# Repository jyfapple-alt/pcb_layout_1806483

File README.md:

# auto_routing README

这份 README 主要做两件事：

1. 用通俗的话解释这个仓库里暴露出来的 MCP tools 是干什么的。
2. 把每个 tool 的入参、返回值、参数意义讲清楚。
3. 顺带把 `.claude/skills` 里的技能做一遍“人话解读”。

这份说明是根据下面这些源码整理出来的，不是凭空猜的：

- `mcp/pcb_routing_server.py`
- `mcp/route_analysis.py`
- `mcp/route_planner.py`
- `mcp/footprint_placement.py`
- `mcp/coordinate_routing.py`
- `mcp/routing_session_store.py`
- `.claude/skills/*/SKILL.md`

---

## 1. 这个仓库的 MCP 到底是什么

这个项目里真正对外暴露 MCP tools 的入口是：

- `mcp/pcb_routing_server.py`

它用的是 `FastMCP`，名字叫：

- `pcb-routing-mcp`

你可以把它理解成一个“会操作 KiCad PCB 的本地工具服务器”。  
LLM 不直接手搓 PCB 文件，而是通过这些 tool 去做：

- 看板子结构
- 分析哪些器件要先 fanout
- 自动放置 footprint
- 生成 routing plan
- 执行自动布线
- 让 LLM 输出坐标形式的走线计划
- 校验 DRC / 连通性 / 悬空 stub

仓库里还有很多 Python 文件，但不是每个 Python 函数都算 MCP tool。  
真正的 MCP tool，是那些被 `@mcp.tool(...)` 装饰过的函数。

当前一共暴露了 **33 个 MCP tool**。

---

## 2. 整体结构怎么理解

可以把这些 tool 分成 5 组：

- **基础检查类**
  看板子、看环境、看文件是否合法。
- **Session 工作流类**
  把一次布线任务做成一个“会话”，方便多次调用之间保留上下文。
- **Footprint 放置类**
  给元件做自动摆放，或者让 LLM 自己出摆放方案。
- **坐标级布线类**
  给 LLM 一份几何上下文，让它直接输出走线点坐标。
- **底层脚本封装类**
  直接封装 `mcp/kicad_routing_tools` 里的 CLI 脚本，例如 fanout、route、DRC 检查等。

---

## 3. 通用规则

在看每个 tool 之前，先记住几个通用规则，后面会反复出现。

### 3.1 路径怎么处理

- 凡是 `pcb_path`、`input_pcb`、`board_path` 这类输入文件参数，都会先检查文件是否存在。
- 相对路径会按**仓库根目录**来解析，不是按当前 shell 所在目录。
- 输出路径参数比如 `output_path`、`output_pcb`、`output_board`，如果传相对路径，也会按仓库根目录解析。

### 3.2 日志放哪里

底层脚本类 tool 会把输出写进：

- `mcp/logs/`

返回里通常会带一个：

- `log_path`

如果自动布线失败，优先看这个日志路径最省事。

### 3.3 Session 放哪里

路由会话会保存在：

- `mcp/routing_sessions/<session_id>/`

每个 session 里会保存：

- 当前工作板文件
- 分析结果
- 路由计划
- 执行历史
- 最近几次校验结果
- 放置/坐标上下文
- 产物路径和日志路径

### 3.4 底层脚本封装的通用返回结构

下面这些 tool 都走统一的 `_run_script(...)` 返回格式：

- `run_routing_script`
- `build_rust_router`
- `list_nets`
- `run_bga_fanout`
- `run_qfn_fanout`
- `route_single_ended`
- `route_differential_pairs`
- `create_power_planes`
- `repair_disconnected_planes`
- `check_connectivity`
- `check_drc`
- `check_orphan_stubs`

它们的返回字段基本一致：

- `success`
  是否成功，底层进程退出码为 0 时通常为 `true`。
- `script`
  实际调用的脚本名，例如 `route.py`。
- `command`
  实际执行的命令数组。
- `cwd`
  运行脚本时的工作目录。
- `returncode`
  底层进程退出码。超时场景会是 `null`。
- `duration_seconds`
  运行耗时。
- `stdout_tail`
  标准输出的最后一段内容。
- `stderr_tail`
  标准错误的最后一段内容。
- `log_path`
  完整日志文件路径。
- `json_summary`
  如果脚本输出了 `JSON_SUMMARY:` 行，这里会解析成 JSON；否则为 `null`。
- `timed_out`
  只有超时返回时才会出现，值为 `true`。

一句话理解：  
这类 tool 负责“跑脚本”，所以重点看 `success`、`log_path`、`json_summary`。

---

## 4. 几个高频数据结构先看懂

后面的 tool 会反复返回这些结构。

### 4.1 Session 对象

`create_routing_session` 和 `get_routing_session` 返回的是完整 session 对象，核心字段有：

- `session_id`
  会话 ID，例如 `rs_xxxxx`。
- `session_name`
  会话显示名。
- `description`
  会话说明。
- `board_path`
  原始板文件路径。
- `working_board_path`
  当前正在操作的板文件路径。后续每做一步，通常都是它在变化。
- `coordinate_mode`
  坐标模式。当前最有意义的是：
  - `algorithm_only`：主要靠算法路由器
  - `llm_coordinates`：允许 LLM 直接给坐标走线
- `placement_mode`
  放置模式。当前最常见的是：
  - `auto`
  - `llm_placement`
- `status`
  当前状态，例如 `created`、`analyzed`、`planned`、`placed`、`executed` 等。
- `created_at` / `updated_at`
  创建和更新时间。
- `session_dir`
  这个 session 自己的目录。
- `output_dir`
  这个 session 默认的输出目录。
- `analysis`
  上一次结构化分析结果。
- `objective`
  这次规划的目标，比如 `autoroute`。
- `constraints`
  规划时使用的约束。
- `proposed_plan`
  上一次生成的 routing plan。
- `execution_history`
  历史执行记录。
- `latest_checks`
  最近一次连通性 / DRC / orphan stub 检查结果。
- `placement_context`
  LLM 放置上下文。
- `latest_placement_validation`
  最近一次摆放方案校验结果。
- `placement_history`
  摆放历史。
- `coordinate_context`
  LLM 坐标布线上下文。
- `latest_coordinate_validation`
  最近一次坐标计划校验结果。
- `coordinate_history`
  坐标布线历史。
- `artifacts`
  产物路径集合，至少包含 `boards` 和 `logs`。
- `notes`
  会话过程中的注释日志。

### 4.2 `analysis` 结构

`analyze_board_for_llm` 返回的核心是 `analysis`，里面常见字段有：

- `pcb_path`
- `board`
  - `total_nets`
  - `named_nets`
  - `total_footprints`
  - `total_segments`
  - `total_vias`
  - `total_zones`
  - `fresh_board`
  - `copper_layers`
  - `board_bounds`
- `zones`
  每个 zone 的 `net_id`、`net_name`、`layer`、`layers`
- `nets`
  每个命名网络的 `net_id`、`name`、`pad_count`
- `ground_nets`
- `power_nets`
- `differential_pairs`
- `fanout_candidates`
  候选密脚器件，包含 `reference`、`footprint`、`pad_count`、`recommended_tool`
- `unrouted_named_nets`
- `high_speed_hints`
  包含 `highest_tier` 和 `matched_nets`
- `placement_hints`
  包含：
  - `footprints_at_origin`
  - `footprints_outside_board`
  - `collapsed_groups`
  - `suggested_refs`
  - `needs_placement`
- `planning_hints`
  包含：
  - `has_existing_ground_zone`
  - `has_diff_pairs`
  - `needs_fanout`
  - `needs_plane_repair_after_routing`
  - `suggested_routing_layers`
  - `suggested_power_nets_for_wide_traces`

### 4.3 `plan` 结构

`propose_routing_plan` 里的 `plan` 长这样：

- `plan_id`
- `generated_at`
- `objective`
- `coordinate_mode`
- `constraints`
- `analysis_snapshot`
  这是分析结果的浓缩版，不是全量 `analysis`
- `steps`
  每一步都是：
  - `step_id`
  - `kind`
  - `reason`
  - `input_board`
  - `output_board`
  - `parameters`

### 4.4 `placement_plan` 结构

LLM 摆放方案需要长这样：

```json
{
  "grid_step": 0.25,
  "placements": [
    {
      "reference": "U1",
      "x": 40.0,
      "y": 42.0,
      "rotation": 0.0
    }
  ]
}
```

字段含义：

- `grid_step`
  建议摆放网格。
- `placements`
  摆放列表。
- `reference`
  器件位号。
- `x` / `y`
  KiCad footprint 原点坐标，不一定是器件物理中心。
- `rotation`
  角度，单位度。

### 4.5 放置校验结果 `validation`

放置类校验结果常见字段：

- `valid`
- `pcb_path`
- `placement_gap`
- `board_margin`
- `placement_count`
- `errors`
- `warnings`
- `placements`
  每个 placement 的摘要，通常包含 `reference`、`x`、`y`、`rotation`、`width`、`height`

### 4.6 `coordinate_plan` 结构

LLM 坐标走线计划需要长这样：

```json
{
  "default_track_width": 0.1,
  "default_via_size": 0.3,
  "default_via_drill": 0.2,
  "grid_step": 0.1,
  "routes": [
    {
      "net": "/EN",
      "track_width": 0.15,
      "points": [
        {"x": 40.5, "y": 22.4, "layer": "F.Cu"},
        {"x": 42.1, "y": 22.4, "layer": "F.Cu"},
        {"x": 42.7, "y": 23.0, "layer": "F.Cu"},
        {"x": 42.7, "y": 24.6, "layer": "F.Cu"},
        {"x": 42.7, "y": 24.6, "layer": "B.Cu"},
        {"x": 44.3, "y": 24.6, "layer": "B.Cu"}
      ]
    }
  ]
}
```

字段含义：

- `default_track_width` / `default_via_size` / `default_via_drill`
  默认线宽和过孔参数。
- `grid_step`
  推荐坐标栅格。
- `routes`
  一组要新加的线路。
- `net`
  网络名。
- `track_width`
  该条 route 自己的线宽。
- `points`
  走线路径点。

注意：

- 相邻两个点 XY 相同但 layer 不同，表示“这里插一个 via”。
- 同层转角不能是直角或更尖，推荐 45 度斜切形成 135 度内角。

### 4.7 坐标校验结果 `validation`

坐标布线校验结果常见字段：

- `valid`
- `pcb_path`
- `defaults`
- `route_summaries`
- `tracks`
- `vias`
- `errors`
- `warnings`
- `normalized_plan`

### 4.8 文件合法性校验 `file_validation`

`validate_kicad_pcb` 以及坐标/摆放 apply 成功后附带的文件校验，核心字段有：

- `valid`
- `pcb_path`
- `kicad_version`
- `net_syntax_mode`
  - `numeric`
  - `name-only`
- `parse_ok`
- `parse_error`
- `pcbnew`
  - `available`
  - `ok`
  - `error`
- `issues`
  常见问题码：
  - `named-net-syntax-in-kicad9`
  - `numeric-net-syntax-in-kicad10`
  - `parser-error`
  - `pcbnew-load-error`

---

## 5. 每个 MCP tool 是干什么的

下面按类别逐个解释。

---

## 5.1 基础检查类

### `inspect_pcb`

**作用**  
快速看一块 `.kicad_pcb` 的整体情况，适合“先摸底”。

**参数**

- `pcb_path` (`str`, 必填)
  要检查的板文件路径。

**返回**

- `pcb_path`
  解析后的绝对路径。
- `total_nets`
- `total_footprints`
- `total_segments`
- `total_vias`
- `total_zones`
- `fresh_board`
  如果没有 track segment，会认为是“新板”。
- `copper_layers`
  板上铜层名列表。
- `zones`
  每个 zone 的摘要。
- `fanout_candidates`
  可能需要先做 fanout 的器件。
- `high_speed_hints`
  高速网络提示。
- `footprints`
  每个 footprint 的简要列表。

**补充说明**

- 这里的 `fanout_candidates[].recommended_tool` 返回的是脚本名：
  - `qfn_fanout.py`
  - `bga_fanout.py`
- 在 session 分析里，类似字段会返回 MCP tool 名：
  - `run_qfn_fanout`
  - `run_bga_fanout`

---

### `router_environment_status`

**作用**  
检查当前 Python 环境、嵌入式工具目录、Rust router 模块是否可用。

**参数**

- 无参数。

**返回**

- `python_executable`
  当前 Python 解释器。
- `project_root`
- `mcp_root`
- `embedded_tools_root`
- `tools_root`
  当前实际使用的工具目录。
- `tools_root_source`
  来源，通常是 `embedded` 或 `env`。
- `tools_root_exists`
- `rust_router_root`
- `rust_router_root_exists`
- `grid_router_module_exists`
- `grid_router_importable`
  能不能 import `grid_router`。
- `grid_router_version`
  仅 import 成功时返回。
- `grid_router_file`
  仅 import 成功时返回。
- `grid_router_error`
  import 失败时返回错误信息。

---

### `validate_kicad_pcb`

**作用**  
检查一个 `.kicad_pcb` 文件在当前 KiCad 版本语法下是不是合法，并尝试解析它。

**参数**

- `pcb_path` (`str`, 必填)
  要校验的板文件。
- `use_pcbnew_if_available` (`bool`, 默认 `false`)
  如果环境里有 `pcbnew`，是否顺带用 `pcbnew.LoadBoard(...)` 再做一次加载测试。

**返回**

- 返回结构见上面的 `file_validation`。

---

## 5.2 Session 工作流类

### `create_routing_session`

**作用**  
创建一个路由会话。后面分析、规划、执行都可以围绕这个 session 来做。

**参数**

- `board_path` (`str`, 必填)
  原始板文件路径。
- `session_name` (`str | None`, 默认 `None`)
  会话名称；不传就用自动生成的 `session_id`。
- `output_dir` (`str | None`, 默认 `None`)
  产物输出目录；不传就写到 session 自己的 `artifacts` 目录。
- `description` (`str | None`, 默认 `None`)
  这次会话的说明文字。
- `coordinate_mode` (`str`, 默认 `"algorithm_only"`)
  坐标模式。一般先用 `algorithm_only`。
- `placement_mode` (`str`, 默认 `"auto"`)
  放置模式。通常 `auto` 就够用。

**返回**

- 返回完整 `session` 对象。

---

### `list_routing_sessions`

**作用**  
列出当前所有可恢复的 routing session。

**参数**

- 无参数。

**返回**

- `session_count`
  会话数量。
- `sessions`
  每个元素是 session 摘要，包含：
  - `session_id`
  - `session_name`
  - `status`
  - `board_path`
  - `working_board_path`
  - `coordinate_mode`
  - `placement_mode`
  - `updated_at`
  - `created_at`

---

### `get_routing_session`

**作用**  
取回某个 session 的完整状态。

**参数**

- `session_id` (`str`, 必填)
  目标会话 ID。

**返回**

- 返回完整 `session` 对象。

---

### `analyze_board_for_llm`

**作用**  
对 session 当前板子做结构化分析，并把结果存进 session。

**参数**

- `session_id` (`str`, 必填)
  目标会话 ID。
- `board_path_override` (`str | None`, 默认 `None`)
  如果想临时指定另外一个板文件来分析，可以传这个；不传就分析 `working_board_path`。

**返回**

- `session_id`
- `analysis`
  结构见前面的 `analysis` 说明。
- `working_board_path`
  本次分析对应的工作板路径。

---

### `propose_routing_plan`

**作用**  
把“目标 + 约束”转换成一个可执行 routing plan。

**参数**

- `session_id` (`str`, 必填)
  目标会话 ID。
- `objective` (`str`, 默认 `"autoroute"`)
  目标描述，比如 `autoroute`、`cleanup`、`route power first` 之类。
- `constraints` (`dict | None`, 默认 `None`)
  路由约束字典。支持的主要键有：
  - `placement_mode`
    是否自动插入放置步骤。常见值：
    - `auto`
    - `force`
  - `place_zero_only`
    自动放置时是否只处理原点/越界器件。
  - `placement_gap`
    footprint 间距。
  - `board_margin`
    与板边保持的 margin。
  - `placement_grid_step`
    放置网格步长。
  - `route_mode`
    路由模式；源码里会影响默认的 `max_iterations` / `max_ripup`。
  - `route_diff_pairs_first`
    是否先布差分对。
  - `prefer_existing_zones`
    是否优先保留已有铜皮/zone。
  - `use_power_planes`
    是否显式要求建 plane；`null` 表示让系统自己判断。
  - `coordinate_mode`
    路由模式，常见为 `algorithm_only` 或 `llm_coordinates`。
  - `layers`
    指定允许使用的铜层。
  - `track_width`
    默认线宽。
  - `clearance`
    默认间距。
  - `power_track_width`
    电源网络推荐宽线宽。
  - `diff_pair_gap`
    差分对间距。
  - `max_iterations`
    底层路由算法最大迭代次数。
  - `max_ripup`
    rip-up 重试强度。
  - `no_bga_zones`
    指定禁用 BGA zone 的器件/区域。
  - `notes`
    备注文本。

**返回**

- `session_id`
- `working_board_path`
- `analysis_snapshot`
  `plan` 内嵌分析摘要的快捷访问。
- `plan`
  完整 plan 结构，见上面的 `plan` 说明。

---

### `apply_routing_plan`

**作用**  
按顺序执行一个 routing plan，并把结果写回 session。

**参数**

- `session_id` (`str`, 必填)
  目标会话 ID。
- `plan` (`dict | None`, 默认 `None`)
  如果传了，就执行这个 plan；不传就执行 session 里保存的 `proposed_plan`。
- `stop_after_step` (`int | None`, 默认 `None`)
  执行到第几步就停，适合分步调试。
- `continue_on_error` (`bool`, 默认 `false`)
  某一步失败后是否继续往后执行。

**返回**

- `session_id`
- `execution_id`
  本次执行 ID。
- `status`
  `completed`、`partial`、`failed` 等。
- `working_board_path`
  执行完成后当前工作板。
- `executed_steps`
  实际执行了多少步。
- `plan_id`
- `latest_checks`
  最近一次各类检查结果。
- `last_step`
  最后一步执行记录，包含：
  - `index`
  - `step_id`
  - `kind`
  - `reason`
  - `input_board`
  - `output_board`
  - `parameters`
  - `started_at`
  - `completed_at`
  - `status`
  - `result`

---

### `analyze_session_failures`

**作用**  
把最近一次 plan 执行失败的原因总结出来，方便下一步修复。

**参数**

- `session_id` (`str`, 必填)
  目标会话 ID。

**返回**

- `session_id`
- `status`
  通常是：
  - `no-execution-history`
  - `healthy`
  - `needs-attention`
- `latest_execution_id`
  最近一次执行 ID。
- `failed_steps`
  每个失败步骤包含：
  - `step_id`
  - `kind`
  - `reason`
  - `success`
  - `returncode`
  - `failed_single`
  - `failed_multipoint`
  - `stdout_tail`
  - `stderr_tail`
  - `log_path`
- `next_actions`
  系统建议的下一步动作。
- `working_board_path`
- `coordinate_mode`
- `placement_mode`

---

### `suggest_next_routing_actions`

**作用**  
基于 session 当前状态，给出“下一步建议做什么”。

**参数**

- `session_id` (`str`, 必填)
  目标会话 ID。

**返回**

- `session_id`
- `status`
- `working_board_path`
- `coordinate_mode`
- `placement_mode`
- `latest_execution_summary`
  本质上就是一份失败/执行总结。
- `suggestions`
  建议动作列表。每个元素一般有：
  - `action`
  - `reason`
  - 以及可选的 `references`、`coordinate_mode` 等补充信息

---

## 5.3 Footprint 放置类

### `auto_place_footprints`

**作用**  
对一块板文件直接做一次启发式自动摆放，不依赖 session。

**参数**

- `pcb_path` (`str`, 必填)
  输入板文件路径。
- `output_path` (`str | None`, 默认 `None`)
  输出板文件路径。不传时会自动生成一个 `<原文件名>_placed.kicad_pcb`。
- `references` (`list[str] | None`, 默认 `None`)
  只摆放这些指定位号；不传就按规则自动挑。
- `zero_only` (`bool`, 默认 `true`)
  是否只处理“明显需要重摆”的器件，比如在原点、越界、严重重叠分组。
- `placement_gap` (`float`, 默认 `1.0`)
  footprint 之间预留间距，单位 mm。
- `board_margin` (`float`, 默认 `0.25`)
  离板边预留的 margin，单位 mm。
- `grid_step` (`float`, 默认 `0.25`)
  自动摆放时的吸附网格。

**返回**

这个 tool 的返回比普通脚本丰富，核心字段有：

- `success`
- `input_path`
- `output_path`
- `placement_plan`
  这次自动生成的摆放方案。
- `validation`
  放置校验结果。
- `placement_count`
  仅成功写出时会有。
- `board_summary`
  仅成功写出时会有，包含 `total_footprints`、`total_segments`、`total_vias`。
- `placed_references`
  实际参与自动放置的器件位号。
- `skipped_references`
  没有被自动放置的位号。
- `strategy`
  当前是 `heuristic_connectivity`。
- `reasoning`
  每个器件为什么放在那个位置的简要说明。
- `flow`
  推断的主布局流向，例如 `left_to_right`。
- `error`
  如果失败会给出错误信息。

---

### `build_llm_placement_context`

**作用**  
构建给 LLM 用的摆放上下文，让模型自己决定器件坐标。

**参数**

- `session_id` (`str`, 必填)
  目标会话 ID。
- `references` (`list[str] | None`, 默认 `None`)
  只给这些位号构建上下文。
- `include_full_context` (`bool`, 默认 `false`)
  是否直接把完整上下文也放到返回里；不传时只返回 summary，并把完整内容保存在 session。

**返回**

- `session_id`
- `working_board_path`
- `placement_mode`
  如果原来是 `auto`，这里通常会切到 `llm_placement`。
- `context_summary`
  摘要字段包括：
  - `available`
  - `pcb_path`
  - `board`
  - `placement_hints`
  - `footprint_count`
  - `references`
  - `roles`
  - `schema_rules`
- `stored_in_session`
  是否已保存进 session。
- `context`
  只有 `include_full_context=true` 时才返回。完整上下文包含：
  - `pcb_path`
  - `board`
  - `placement_hints`
  - `footprints`
  - `connections`
  - `schema_hint`

---

### `get_llm_placement_context`

**作用**  
从 session 里把之前保存的 placement context 读出来。

**参数**

- `session_id` (`str`, 必填)
  目标会话 ID。
- `include_full_context` (`bool`, 默认 `false`)
  是否把完整上下文一起返回。

**返回**

- `session_id`
- `working_board_path`
- `placement_mode`
- `context_summary`
- `stored_in_session`
- `context`
  只有 `include_full_context=true` 且 session 里确实有上下文时返回。

---

### `validate_llm_placement_plan`

**作用**  
检查一份 LLM 摆放方案是否合法，但不改板文件。

**参数**

- `session_id` (`str`, 必填)
  目标会话 ID。
- `placement_plan` (`dict`, 必填)
  摆放方案，结构见前面的 `placement_plan`。
- `placement_gap` (`float`, 默认 `1.0`)
  校验时要求的最小间距。
- `board_margin` (`float`, 默认 `0.25`)
  校验时离板边的 margin。

**返回**

- `session_id`
- `working_board_path`
- `validation`
  放置校验结果，结构见前文。

---

### `apply_llm_placement_plan`

**作用**  
把一份 LLM 给出的摆放方案真正写进板文件，并更新 session。

**参数**

- `session_id` (`str`, 必填)
  目标会话 ID。
- `placement_plan` (`dict`, 必填)
  摆放方案。
- `output_board` (`str | None`, 默认 `None`)
  输出板路径。不传时会自动在 session 输出目录里生成文件。
- `placement_gap` (`float`, 默认 `1.0`)
- `board_margin` (`float`, 默认 `0.25`)
- `refresh_analysis` (`bool`, 默认 `true`)
  成功后是否重新分析板子。

**返回**

- `session_id`
- `placement_mode`
- `working_board_path`
- `result`
  `result` 的核心字段有：
  - `success`
  - `input_path`
  - `output_path`
  - `validation`
  - `placement_count`
  - `board_summary`
  - `file_validation`
  - `error`

---

### `auto_place_session_footprints`

**作用**  
在 session 里对当前工作板做自动摆放。这通常是实际流程里更推荐的放置入口。

**参数**

- `session_id` (`str`, 必填)
  目标会话 ID。
- `output_board` (`str | None`, 默认 `None`)
  输出板路径；不传时自动生成。
- `references` (`list[str] | None`, 默认 `None`)
  指定只摆某些器件。
- `zero_only` (`bool`, 默认 `true`)
  是否只处理明显需要重摆的器件。
- `placement_gap` (`float`, 默认 `1.0`)
- `board_margin` (`float`, 默认 `0.25`)
- `grid_step` (`float`, 默认 `0.25`)
- `refresh_analysis` (`bool`, 默认 `true`)
  成功后是否自动刷新 session 的 `analysis`。

**返回**

- `session_id`
- `working_board_path`
- `result`
  里面基本就是 `auto_place_footprints` 的结果，再额外附带：
  - `file_validation`

---

## 5.4 坐标级布线类

### `build_llm_coordinate_context`

**作用**  
构建给 LLM 用的“几何布线上下文”，让模型按点坐标输出走线。

**参数**

- `session_id` (`str`, 必填)
  目标会话 ID。
- `nets` (`list[str] | None`, 默认 `None`)
  精确指定要处理的网络名。
- `net_patterns` (`list[str] | None`, 默认 `None`)
  通配符模式，底层用 `fnmatch` 匹配，比如 `USB*`。
- `max_pads_per_net` (`int`, 默认 `12`)
  每个网络最多返回多少 pad，防止上下文爆炸。
- `max_segments_per_net` (`int`, 默认 `20`)
- `max_vias_per_net` (`int`, 默认 `12`)
- `max_stubs_per_net` (`int`, 默认 `12`)
- `include_full_context` (`bool`, 默认 `false`)
  是否把完整上下文直接返回。

**返回**

- `session_id`
- `working_board_path`
- `coordinate_mode`
  如果之前是 `algorithm_only`，这里通常会切到 `llm_coordinates`。
- `context_summary`
  摘要字段包括：
  - `available`
  - `pcb_path`
  - `board`
  - `defaults`
  - `net_count`
  - `net_names`
  - `per_net_counts`
  - `schema_rules`
- `stored_in_session`
- `context`
  仅 `include_full_context=true` 时返回。完整上下文包含：
  - `pcb_path`
  - `board`
  - `defaults`
  - `nets`
  - `schema_hint`

---

### `get_llm_coordinate_context`

**作用**  
把 session 里已经保存的坐标布线上下文取出来。

**参数**

- `session_id` (`str`, 必填)
  目标会话 ID。
- `include_full_context` (`bool`, 默认 `false`)
  是否把完整上下文一起返回。

**返回**

- `session_id`
- `working_board_path`
- `coordinate_mode`
- `context_summary`
- `stored_in_session`
- `context`
  仅 `include_full_context=true` 且上下文存在时返回。

---

### `validate_llm_coordinate_plan`

**作用**  
检查一份 LLM 坐标走线计划是否合法，但不修改板文件。

**参数**

- `session_id` (`str`, 必填)
  目标会话 ID。
- `coordinate_plan` (`dict`, 必填)
  坐标走线方案，结构见前文。
- `endpoint_tolerance` (`float`, 默认 `0.2`)
  端点贴合到已有 pad/via/segment/stub 的容差，单位 mm。
- `grid_tolerance` (`float`, 默认 `0.01`)
  允许偏离 grid 的容差。

**返回**

- `session_id`
- `working_board_path`
- `validation`
  坐标校验结果，结构见前文。

---

### `apply_llm_coordinate_plan`

**作用**  
把 LLM 输出的坐标走线计划真正写入板文件，并可选地立刻做检查。

**参数**

- `session_id` (`str`, 必填)
  目标会话 ID。
- `coordinate_plan` (`dict`, 必填)
  坐标走线方案。
- `output_board` (`str | None`, 默认 `None`)
  输出板路径；不传时自动生成。
- `endpoint_tolerance` (`float`, 默认 `0.2`)
- `grid_tolerance` (`float`, 默认 `0.01`)
- `run_checks` (`bool`, 默认 `true`)
  成功后是否自动跑连通性、DRC、orphan stub 检查。
- `clearance` (`float | None`, 默认 `None`)
  如果要自动做 DRC，这里可以显式指定 clearance；不传就尝试从 session 的 `constraints` 里拿。

**返回**

- `session_id`
- `coordinate_mode`
- `working_board_path`
- `result`
  核心字段有：
  - `success`
  - `pcb_path`
  - `output_path`
  - `track_count`
  - `via_count`
  - `validation`
  - `file_validation`
  - `auto_repair`
- `checks`
  如果 `run_checks=true` 且写板成功，会包含：
  - `check_connectivity`
  - `check_drc`
  - `check_orphan_stubs`
  这三个检查结果都走统一 `_run_script` 结构。

**补充说明**

- 这个 tool 会自动尝试修复 KiCad 9/10 之间的 net 语法差异。
- 修复结果会体现在 `result.auto_repair` 里。

---

## 5.5 底层脚本封装类

### `run_routing_script`

**作用**  
直接运行一个受支持的底层脚本。适合“现成 dedicated tool 没暴露某个 flag”的场景。

**参数**

- `script_name` (`str`, 必填)
  允许的脚本名只有这些：
  - `build_router.py`
  - `list_nets.py`
  - `bga_fanout.py`
  - `qfn_fanout.py`
  - `route.py`
  - `route_diff.py`
  - `route_planes.py`
  - `route_disconnected_planes.py`
  - `check_connected.py`
  - `check_drc.py`
  - `check_orphan_stubs.py`
- `args` (`list[str] | None`, 默认 `None`)
  原始命令行参数列表。
- `timeout_seconds` (`int`, 默认 `600`)
  超时时间。
- `cwd` (`str | None`, 默认 `None`)
  运行目录；不传时由服务端决定默认目录。

**返回**

- 统一 `_run_script` 结构。

---

### `build_rust_router`

**作用**  
编译或清理 Rust router 模块。

**参数**

- `clean` (`bool`, 默认 `false`)
  是否执行清理模式，相当于给底层 `build_router.py` 传 `--clean`。
- `timeout_seconds` (`int`, 默认 `900`)
  编译超时。

**返回**

- 统一 `_run_script` 结构。

---

### `list_nets`

**作用**  
查看板上的网络信息，可以做 component pad mapping、差分对探测、电源网筛选等。

**参数**

- `pcb_path` (`str`, 必填)
  板文件路径。
- `component` (`str | None`, 默认 `None`)
  只看某个元件。
- `pads` (`bool`, 默认 `false`)
  是否展开 pad 映射。
- `diff_pairs` (`bool`, 默认 `false`)
  是否重点看差分对。
- `power` (`bool`, 默认 `false`)
  是否重点看电源网。
- `top` (`int`, 默认 `10`)
  返回前多少项。
- `pattern` (`str | None`, 默认 `None`)
  网络名模式过滤。
- `extra_args` (`list[str] | None`, 默认 `None`)
  额外原始参数。
- `timeout_seconds` (`int`, 默认 `120`)

**返回**

- 统一 `_run_script` 结构。

---

### `run_bga_fanout`

**作用**  
对 BGA / PGA 器件做 escape routing。

**参数**

- `pcb_path` (`str`, 必填)
  输入板文件。
- `output_path` (`str | None`, 默认 `None`)
  输出板文件。
- `component` (`str | None`, 默认 `None`)
  指定只对某个器件做 fanout。
- `layers` (`list[str] | None`, 默认 `None`)
  fanout 可使用的层。
- `nets` (`list[str] | None`, 默认 `None`)
  只处理这些网络。
- `diff_pairs` (`list[str] | None`, 默认 `None`)
  差分对网络列表。
- `track_width` (`float | None`, 默认 `None`)
- `clearance` (`float | None`, 默认 `None`)
- `via_size` (`float | None`, 默认 `None`)
- `via_drill` (`float | None`, 默认 `None`)
- `diff_pair_gap` (`float | None`, 默认 `None`)
- `exit_margin` (`float | None`, 默认 `None`)
  fanout 出口留量。
- `primary_escape` (`str | None`, 默认 `None`)
  首选逃线方向/策略，对应底层 `--primary-escape`。
- `force_escape_direction` (`bool`, 默认 `false`)
  是否强制使用指定逃线方向。
- `rebalance_escape` (`bool`, 默认 `false`)
  是否启用 escape 重平衡。
- `check_for_previous` (`bool`, 默认 `false`)
  是否检查之前已有的 fanout 痕迹。
- `no_inner_top_layer` (`bool`, 默认 `false`)
  是否禁用某个顶部内层参与 fanout。
- `extra_args` (`list[str] | None`, 默认 `None`)
- `timeout_seconds` (`int`, 默认 `300`)

**返回**

- 统一 `_run_script` 结构。

---

### `run_qfn_fanout`

**作用**  
给 QFN / QFP 这类四周出脚封装做 stub fanout。

**参数**

- `pcb_path` (`str`, 必填)
- `output_path` (`str | None`, 默认 `None`)
- `component` (`str | None`, 默认 `None`)
- `layer` (`str | None`, 默认 `None`)
  fanout 所在层。
- `width` (`float | None`, 默认 `None`)
  fanout 线宽。
- `extension` (`float | None`, 默认 `None`)
  fanout stub 延伸长度。
- `nets` (`list[str] | None`, 默认 `None`)
- `extra_args` (`list[str] | None`, 默认 `None`)
- `timeout_seconds` (`int`, 默认 `300`)

**返回**

- 统一 `_run_script` 结构。

---

### `route_single_ended`

**作用**  
执行单端网络自动布线，对应底层 `route.py`。

**参数**

- `input_pcb` (`str`, 必填)
  输入板文件。
- `output_pcb` (`str | None`, 默认 `None`)
  输出板文件。
- `nets` (`list[str] | None`, 默认 `None`)
  只布这些网络；常见也会传 `["*"]` 表示全部。
- `component` (`str | None`, 默认 `None`)
  只围绕某个元件相关网络。
- `ordering` (`str | None`, 默认 `None`)
  网络处理顺序策略。
- `direction` (`str | None`, 默认 `None`)
  主布线方向偏好。
- `layers` (`list[str] | None`, 默认 `None`)
  允许使用的层。
- `no_bga_zones` (`list[str] | None`, 默认 `None`)
  哪些器件/区域不要建 BGA zones。
- `track_width` (`float | None`, 默认 `None`)
- `impedance` (`float | None`, 默认 `None`)
- `clearance` (`float | None`, 默认 `None`)
- `via_size` (`float | None`, 默认 `None`)
- `via_drill` (`float | None`, 默认 `None`)
- `power_nets` (`list[str] | None`, 默认 `None`)
  哪些网络按电源网处理。
- `power_nets_widths` (`list[float] | None`, 默认 `None`)
  与 `power_nets` 一一对应的宽线宽。
- `grid_step` (`float | None`, 默认 `None`)
- `max_iterations` (`int | None`, 默认 `None`)
- `max_ripup` (`int | None`, 默认 `None`)
- `add_teardrops` (`bool`, 默认 `false`)
- `debug_lines` (`bool`, 默认 `false`)
- `verbose` (`bool`, 默认 `false`)
- `extra_args` (`list[str] | None`, 默认 `None`)
- `timeout_seconds` (`int`, 默认 `900`)

**返回**

- 统一 `_run_script` 结构。

---

### `route_differential_pairs`

**作用**  
执行差分对自动布线，对应底层 `route_diff.py`。

**参数**

- `input_pcb` (`str`, 必填)
- `output_pcb` (`str | None`, 默认 `None`)
- `nets` (`list[str] | None`, 默认 `None`)
  差分对网络名列表。
- `ordering` (`str | None`, 默认 `None`)
- `direction` (`str | None`, 默认 `None`)
- `layers` (`list[str] | None`, 默认 `None`)
- `no_bga_zones` (`list[str] | None`, 默认 `None`)
- `track_width` (`float | None`, 默认 `None`)
- `impedance` (`float | None`, 默认 `None`)
- `clearance` (`float | None`, 默认 `None`)
- `via_size` (`float | None`, 默认 `None`)
- `via_drill` (`float | None`, 默认 `None`)
- `diff_pair_gap` (`float | None`, 默认 `None`)
- `max_iterations` (`int | None`, 默认 `None`)
- `max_ripup` (`int | None`, 默认 `None`)
- `diff_pair_intra_match` (`bool`, 默认 `false`)
  是否启用对内匹配。
- `no_gnd_vias` (`bool`, 默认 `false`)
  是否禁用自动 GND via。
- `add_teardrops` (`bool`, 默认 `false`)
- `debug_lines` (`bool`, 默认 `false`)
- `verbose` (`bool`, 默认 `false`)
- `extra_args` (`list[str] | None`, 默认 `None`)
- `timeout_seconds` (`int`, 默认 `900`)

**返回**

- 统一 `_run_script` 结构。

---

### `create_power_planes`

**作用**  
创建铜皮 plane，或者给 GND 加回流 via，对应底层 `route_planes.py`。

**参数**

- `input_pcb` (`str`, 必填)
- `output_pcb` (`str | None`, 默认 `None`)
- `nets` (`list[str] | None`, 默认 `None`)
  主要 plane 的网络。
- `plane_layers` (`list[str] | None`, 默认 `None`)
  plane 生成在哪些层。
- `layers` (`list[str] | None`, 默认 `None`)
  工具允许操作的层。
- `track_width` (`float | None`, 默认 `None`)
- `clearance` (`float | None`, 默认 `None`)
- `zone_clearance` (`float | None`, 默认 `None`)
  zone 自己的 clearance。
- `via_size` (`float | None`, 默认 `None`)
- `via_drill` (`float | None`, 默认 `None`)
- `grid_step` (`float | None`, 默认 `None`)
- `power_nets` (`list[str] | None`, 默认 `None`)
  作为宽线电源网处理的网络。
- `power_nets_widths` (`list[float] | None`, 默认 `None`)
- `add_gnd_vias` (`bool`, 默认 `false`)
  是否添加回流 GND vias。
- `gnd_via_net` (`str | None`, 默认 `None`)
  GND via 所属网络。
- `gnd_via_distance` (`float | None`, 默认 `None`)
  GND via 间距。
- `rip_blocker_nets` (`bool`, 默认 `false`)
  是否 rip 掉阻挡 plane 的网络。
- `reroute_ripped_nets` (`bool`, 默认 `false`)
  被 rip 掉后是否重布。
- `add_teardrops` (`bool`, 默认 `false`)
- `debug_lines` (`bool`, 默认 `false`)
- `verbose` (`bool`, 默认 `false`)
- `extra_args` (`list[str] | None`, 默认 `None`)
- `timeout_seconds` (`int`, 默认 `900`)

**返回**

- 统一 `_run_script` 结构。

---

### `repair_disconnected_planes`

**作用**  
修复被切碎或断开的铜皮区域，对应底层 `route_disconnected_planes.py`。

**参数**

- `input_pcb` (`str`, 必填)
- `output_pcb` (`str | None`, 默认 `None`)
- `nets` (`list[str] | None`, 默认 `None`)
- `plane_layers` (`list[str] | None`, 默认 `None`)
- `layers` (`list[str] | None`, 默认 `None`)
- `track_width` (`float | None`, 默认 `None`)
- `clearance` (`float | None`, 默认 `None`)
- `zone_clearance` (`float | None`, 默认 `None`)
- `via_size` (`float | None`, 默认 `None`)
- `via_drill` (`float | None`, 默认 `None`)
- `grid_step` (`float | None`, 默认 `None`)
- `max_iterations` (`int | None`, 默认 `None`)
- `dry_run` (`bool`, 默认 `false`)
  只模拟，不实际写结果。
- `debug_lines` (`bool`, 默认 `false`)
- `verbose` (`bool`, 默认 `false`)
- `extra_args` (`list[str] | None`, 默认 `None`)
- `timeout_seconds` (`int`, 默认 `900`)

**返回**

- 统一 `_run_script` 结构。

---

### `check_connectivity`

**作用**  
检查网络是否真正连通，对应底层 `check_connected.py`。

**参数**

- `pcb_path` (`str`, 必填)
- `nets` (`list[str] | None`, 默认 `None`)
  只检查这些网络。
- `component` (`str | None`, 默认 `None`)
  只看某个器件相关的连通性。
- `tolerance` (`float | None`, 默认 `None`)
  连通判断容差。
- `quiet` (`bool`, 默认 `false`)
- `verbose` (`bool`, 默认 `false`)
- `routed_only` (`bool`, 默认 `false`)
  只检查已经布过的部分。
- `extra_args` (`list[str] | None`, 默认 `None`)
- `timeout_seconds` (`int`, 默认 `120`)

**返回**

- 统一 `_run_script` 结构。

---

### `check_drc`

**作用**  
做 DRC / clearance 相关检查，对应底层 `check_drc.py`。

**参数**

- `pcb_path` (`str`, 必填)
- `clearance` (`float | None`, 默认 `None`)
- `hole_to_hole_clearance` (`float | None`, 默认 `None`)
- `board_edge_clearance` (`float | None`, 默认 `None`)
- `clearance_margin` (`float | None`, 默认 `None`)
- `nets` (`list[str] | None`, 默认 `None`)
  只检查这些网络。
- `debug_lines` (`bool`, 默认 `false`)
- `quiet` (`bool`, 默认 `false`)
- `extra_args` (`list[str] | None`, 默认 `None`)
- `timeout_seconds` (`int`, 默认 `120`)

**返回**

- 统一 `_run_script` 结构。

---

### `check_orphan_stubs`

**作用**  
检测悬空的 trace stub，对应底层 `check_orphan_stubs.py`。

**参数**

- `input_pcb` (`str`, 必填)
- `compare_file` (`str | None`, 默认 `None`)
  对比参考板文件。
- `net` (`str | None`, 默认 `None`)
  只查某个网络。
- `layer` (`str | None`, 默认 `None`)
  只查某层。
- `compare` (`bool`, 默认 `false`)
  是否启用对比模式。
- `extra_args` (`list[str] | None`, 默认 `None`)
- `timeout_seconds` (`int`, 默认 `120`)

**返回**

- 统一 `_run_script` 结构。

---

## 6. 推荐工作流

如果你只是想“让系统自己把板子分析、规划、布线尽量走通”，推荐顺序是：

1. `router_environment_status`
2. 如果 `grid_router_importable=false`，调用 `build_rust_router`
3. `create_routing_session`
4. `analyze_board_for_llm`
5. 如果 `analysis.placement_hints.needs_placement=true`，调用 `auto_place_session_footprints`
6. 再次 `analyze_board_for_llm`
7. `propose_routing_plan`
8. `apply_routing_plan`
9. `analyze_session_failures`
10. `suggest_next_routing_actions`

如果你只想“摆元件，不布线”，主线是：

1. `create_routing_session`
2. `analyze_board_for_llm`
3. `auto_place_session_footprints`

如果你想“让 LLM 亲自给坐标走线”，主线是：

1. `create_routing_session`
2. `analyze_board_for_llm`
3. 必要时先做放置
4. `build_llm_coordinate_context`
5. `validate_llm_coordinate_plan`
6. `apply_llm_coordinate_plan`

---

## 7. `.claude/skills` 里面的技能解读

这个目录里现在能看到 5 个技能：

- `route-kicad-pcb-mcp`
- `place-kicad-footprints-mcp`
- `compute-kicad-route-coordinates`
- `find-skills`
- `skill-creator`

前 3 个是本项目最相关的 PCB 技能。  
后 2 个更像“通用技能”，不是专门给 KiCad 项目写的。

---

### `route-kicad-pcb-mcp`

**一句话理解**  
这是“总控技能”。如果目标是把一块 KiCad 板从分析一路推进到布线、检查、重试，它就是主技能。

**它主要负责什么**

- 调用本地 MCP server，而不是随便跑 shell
- 用 session 工作流把整件事串起来
- 先分析、后放置、再规划、再执行
- 失败了以后，再读失败摘要并决定下一步

**它推荐的主流程**

```text
create_routing_session
-> analyze_board_for_llm
-> auto_place_session_footprints（如果需要）
-> analyze_board_for_llm
-> propose_routing_plan
-> apply_routing_plan
-> analyze_session_failures
-> suggest_next_routing_actions
```

**这个技能强调的重点**

- 先分析，不要一上来就乱布线
- 如果 footprint 在 `(0,0)` 或者出板边，先摆放
- 有 BGA / QFN / QFP 先 fanout
- 差分对先于单端线
- 默认优先用 session 流程，不鼓励直接乱调底层脚本
- 失败后优先看日志和失败摘要，不要盲改参数

**适合什么时候用**

- 你想“整体推进一块板”
- 你希望让模型自动决定顺序和策略
- 你想保留过程上下文和历史记录

**不太适合什么时候用**

- 你只想单独摆几个器件
- 你只想手工微调 1~2 根关键线的坐标

---

### `place-kicad-footprints-mcp`

**一句话理解**  
这是“先摆元件”的专项技能。

**它主要负责什么**

- 判断当前板是不是应该先摆元件
- 调 `auto_place_session_footprints` 做默认自动摆放
- 如果自动摆放不够，再切到 `build_llm_placement_context -> validate -> apply`

**它的核心理念**

- 不要死记某块板的旧坐标
- 摆放要根据当前板形、器件尺寸、网络角色、连接关系实时推断
- KiCad 的 `(at x y)` 是 footprint 原点，不一定是封装中心
- 连接器尽量靠边
- 电源 IC 要处在电源流的关键位置
- 电感、电容、反馈件要围绕它服务的 IC 引脚放
- 布局不能只“不重叠”，还要给后续布线留通道

**适合什么时候用**

- 板子还是 fresh board
- 一堆 footprint 都堆在 `(0,0)`
- footprint 跑到板框外面去了
- 你明确想“先放置，再布线”

**它和 `route-kicad-pcb-mcp` 的关系**

- 它更专注于 placement
- 一般可以看作前置步骤
- 摆完以后，再回到 `route-kicad-pcb-mcp`

---

### `compute-kicad-route-coordinates`

**一句话理解**  
这是“让 LLM 直接出走线点坐标”的专项技能。

**它主要负责什么**

- 为少量关键网络构建坐标级几何上下文
- 让模型输出结构化 `coordinate_plan`
- 强调走线几何质量，而不是只求连上

**它特别强调的规则**

- 只适合少量网络，不适合整板大规模 autoroute
- 起点终点要贴到真实导体上
- 同层转角必须是钝角
- 不允许 `horizontal -> vertical` 直接拐 90 度
- 该插 via 的地方要用“同 XY、不同 layer”的点对表示
- 每条网络要单独选线宽，不要全板一刀切

**它最重要的额外思想**

它不只是让你“给坐标”，还要求你先按电气角色给网络分类：

- 电源输入
- 开关节点
- 电源输出
- 地回流 stub
- 控制/普通信号
- 高速/差分

然后按网络角色选不同线宽。

**适合什么时候用**

- 只想手工修 1~2 根关键线
- 自动布线大体完成了，剩下一点点难线
- 想让模型直接表达明确几何，而不是只给策略

**不太适合什么时候用**

- BGA 密集逃线
- 很长的总线
- 整板完全未布线

---

### `find-skills`

**一句话理解**  
这是一个“去技能市场里找现成技能”的通用技能，不是 PCB 专项技能。

**它主要负责什么**

- 当用户说“有没有 skill 能做 X”时，去搜索技能
- 用 `npx skills find ...` 查找
- 告诉用户技能来源和安装命令
- 安装前必须提醒安全风险并征得确认

**它的使用场景**

- 你想扩展 Codex/Claude 的能力
- 你怀疑社区里已经有人做了现成技能

**这个技能的重点**

- 第三方 skill 本质上是代码，要提醒安全风险
- 不能静默安装
- 要先给用户看来源链接

---

### `skill-creator`

**一句话理解**  
这是一个“帮你创建、测试、迭代技能”的通用技能。

**它主要负责什么**

- 帮用户定义 skill 的目标、触发条件、输出格式
- 写 `SKILL.md`
- 设计测试 prompt
- 跑评估、看结果、收集反馈
- 迭代优化 skill
- 最后再优化 description，让 skill 更容易被正确触发

**它的工作方法**

- 先搞清楚 skill 要做什么
- 再写草稿
- 再做测试
- 再根据反馈改
- 一轮一轮迭代

**这个技能特别适合**

- 你想把某个固定工作流沉淀成一个 skill
- 你已经有 skill 初稿，但想做系统化打磨
- 你想给 skill 做 benchmark / eval

**和本项目的关系**

- 它不是路由技能本身
- 更像“造技能的工具”
- 如果以后你想把这个仓库里的某套 routing / placement 流程再封装成新的 skill，它会很有用

---

## 8. 这些技能之间怎么搭配

最常见的搭配关系可以这么理解：

- **`route-kicad-pcb-mcp`**
  主流程技能，负责整体推进。
- **`place-kicad-footprints-mcp`**
  前置专项技能，先把元件摆明白。
- **`compute-kicad-route-coordinates`**
  后期精修技能，只处理少量需要人工几何控制的网络。
- **`find-skills`**
  去外部找更多能力。
- **`skill-creator`**
  自己造新技能或改现有技能。

一句话版本：

- 想“整体跑通”就用 `route-kicad-pcb-mcp`
- 想“先摆元件”就用 `place-kicad-footprints-mcp`
- 想“手工级坐标微调”就用 `compute-kicad-route-coordinates`

---

## 9. 最后给一个快速索引

如果你只是想记住每个 tool 最像什么，可以看这个速查表：

- `inspect_pcb`
  看板子体检报告
- `router_environment_status`
  看环境有没有准备好
- `create_routing_session`
  开一个任务会话
- `list_routing_sessions`
  看有哪些任务会话
- `get_routing_session`
  看某个任务会话详情
- `analyze_board_for_llm`
  给模型做结构化分析
- `propose_routing_plan`
  生成执行计划
- `apply_routing_plan`
  跑计划
- `analyze_session_failures`
  总结失败原因
- `suggest_next_routing_actions`
  建议下一步
- `auto_place_footprints`
  单次自动摆件
- `build_llm_placement_context`
  给模型准备摆件上下文
- `get_llm_placement_context`
  读取摆件上下文
- `validate_llm_placement_plan`
  检查摆件方案
- `apply_llm_placement_plan`
  应用摆件方案
- `auto_place_session_footprints`
  在 session 里自动摆件
- `build_llm_coordinate_context`
  给模型准备坐标走线上下文
- `get_llm_coordinate_context`
  读取坐标上下文
- `validate_kicad_pcb`
  检查板文件是否合法
- `validate_llm_coordinate_plan`
  检查坐标走线方案
- `apply_llm_coordinate_plan`
  应用坐标走线方案
- `run_routing_script`
  直接跑底层脚本
- `build_rust_router`
  编译 Rust router
- `list_nets`
  看网络信息
- `run_bga_fanout`
  做 BGA fanout
- `run_qfn_fanout`
  做 QFN/QFP fanout
- `route_single_ended`
  单端自动布线
- `route_differential_pairs`
  差分对自动布线
- `create_power_planes`
  建 plane / 加地回流 via
- `repair_disconnected_planes`
  修断开的 plane
- `check_connectivity`
  查连通性
- `check_drc`
  查 DRC
- `check_orphan_stubs`
  查悬空 stub

---

## 10. 结论

这个仓库不是“一个单一自动布线脚本”，而是把 PCB 自动处理拆成了三层：

- **分析层**
  看懂板子现在是什么状态。
- **计划层**
  决定接下来先做什么、后做什么。
- **执行层**
  真的去放置、fanout、布线、校验。

`.claude/skills` 则是在这三层外面又加了一层“工作流指导”：

- 哪些时候该先放置
- 哪些时候该走 session 流程
- 哪些时候该让 LLM 直接给坐标
- 哪些时候该重试、该调参、该回退

如果你后面还想继续，我可以在这份 README 的基础上再帮你补两样东西：

1. 给每个 tool 加一段“典型调用示例”。
2. 另外整理一份“从零开始路由一块板的实战教程”。

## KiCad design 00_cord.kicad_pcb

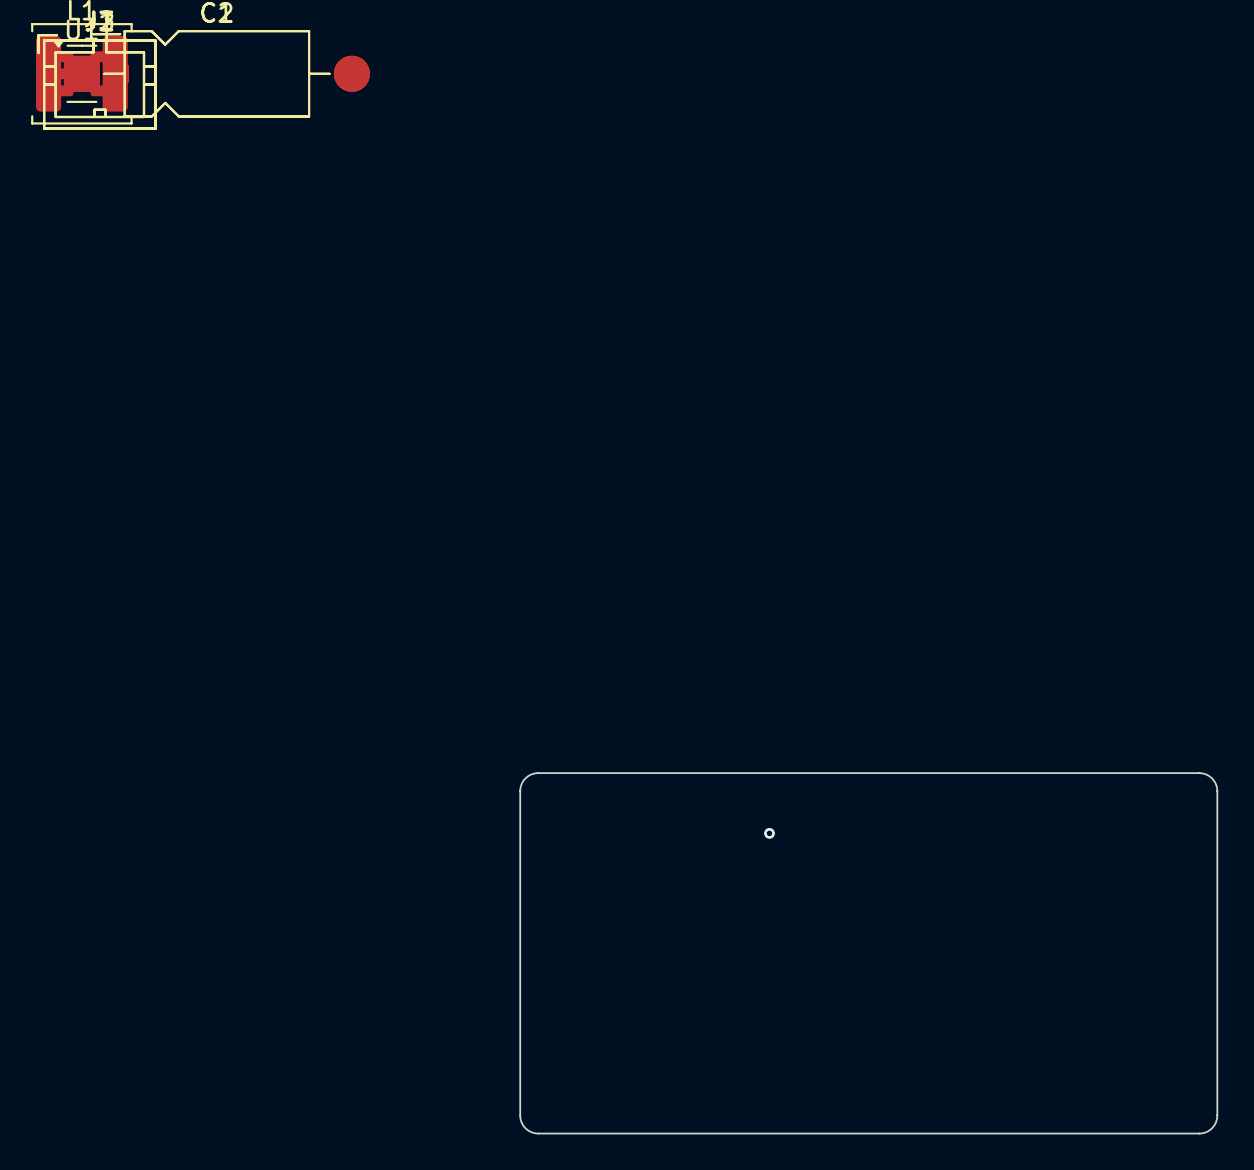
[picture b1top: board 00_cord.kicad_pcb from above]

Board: 2 copper layers, 38.7 x 20.0 mm, 7 parts (0 on the bottom side), 5 nets, no tracks yet.

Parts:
C1, C2: 10uF; CP_Axial_L10.0mm_D4.5mm_P15.00mm_Horizontal
J1, J2, J3: Conn_01x02; TE_440054-2_1x02_P2.00mm_Vertical
L1: 10uH; L_APV_ANR5020
U1: TPS62204DBV; SOT-23-5

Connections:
/EN: J3.1, U1.3 (EN)
/VIN: C1.1, J1.1, U1.1 (VI)
/VOUT: C2.2, J2.1, L1.2, U1.4 (FB)
GND: C1.2, C2.1, J1.2, J2.2, J3.2, U1.2 (GND)
unnamed: L1.1, U1.5 (SW)

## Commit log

2026-04-21 准备开发mcp程序
2026-04-21 开发LLM布线
2026-04-21 完成LLM自plan
2026-04-21 添加LLM布线
2026-04-21 基本完成mcp llm走线
2026-04-21 优化布线skill
2026-04-22 优化布线直角问题
